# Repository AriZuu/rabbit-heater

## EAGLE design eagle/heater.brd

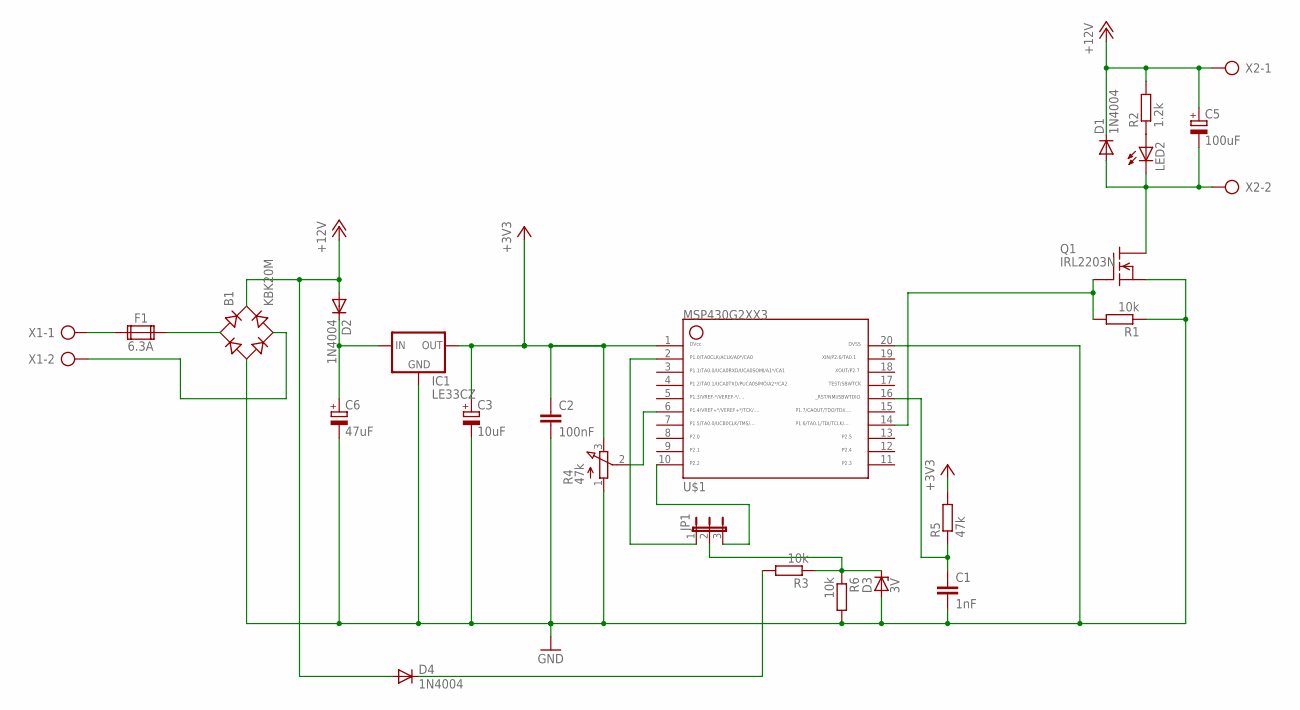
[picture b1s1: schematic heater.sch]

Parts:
B1: KBK20M; SKB32
C1: 1nF; C050-024X044
C2: 100nF; C050-024X044
C3: 10uF; E2,5-6E
C5: 100uF; E2,5-6E
C6: 47uF; E2,5-6E
D1, D2, D4: 1N4004; DO41-10
D3: 3V; DO35Z10
F1: 6.3A; FUSE1
IC1: LE33CZ; TO92
JP1: JP2W
LED2: LED5MM
Q1: IRL2203N; TO220
R1, R3, R6: 10k; 0207/10
R2: 1.2k; 0207/10
R4: 47k; 3RP/1610N
R5: 47k; 0207/10
U$1: MSP430G2533; N20
X1, X2: AK500/2

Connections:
+3V3: C2.1, C3.+, IC1.1 (OUT), R4.3 (E), R5.2, U$1.1
+12V: B1.+, C5.+, D1.C, D2.A, D4.A, R2.2, X2.1
GND: B1.-, C1.2, C2.2, C3.-, C6.-, D3.A, IC1.2 (GND), Q1.3 (S), R1.1, R4.1 (A), R6.2, U$1.20
unnamed: F1.1A, X1.1
unnamed: B1.AC1, F1.2A
unnamed: B1.AC2, X1.2
unnamed: LED2.A, R2.1
unnamed: Q1.1 (G), R1.2, U$1.14
unnamed: R4.2 (S), U$1.6
unnamed: C5.-, D1.A, LED2.K (C), Q1.2 (D), X2.2
unnamed: D3.C, JP1.2, R3.1, R6.1
unnamed: C1.1, R5.1, U$1.16
unnamed: D4.C, R3.2
unnamed: C6.+, D2.C, IC1.3 (IN)
unnamed: JP1.3, U$1.10
unnamed: JP1.1, U$1.2

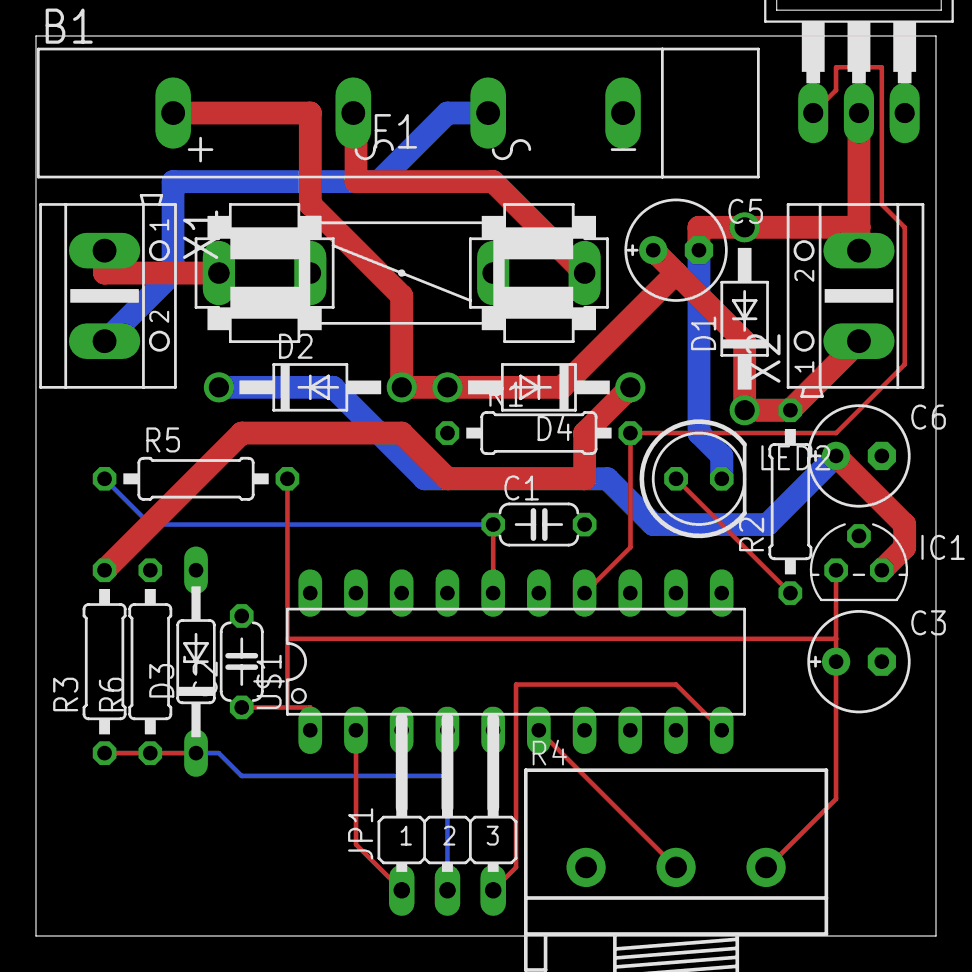
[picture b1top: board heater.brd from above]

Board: 2 copper layers, 50.0 x 50.0 mm, 24 parts (0 on the bottom side), 16 nets.

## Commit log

2013-08-23 Add rabbit-heater project.
2013-08-23 Delay MOSFET gate change until input voltage reaches zero (about zero).
2013-08-23 Turn MOSFET off at start of program.
2013-08-23 Add dist target.
2013-08-23 Initialize unused pins as inputs with pull-down.
2013-08-23 Copyright update.
2013-11-10 Eagle files for heater circuit board.
2013-11-10 Add rough ltspice model.
